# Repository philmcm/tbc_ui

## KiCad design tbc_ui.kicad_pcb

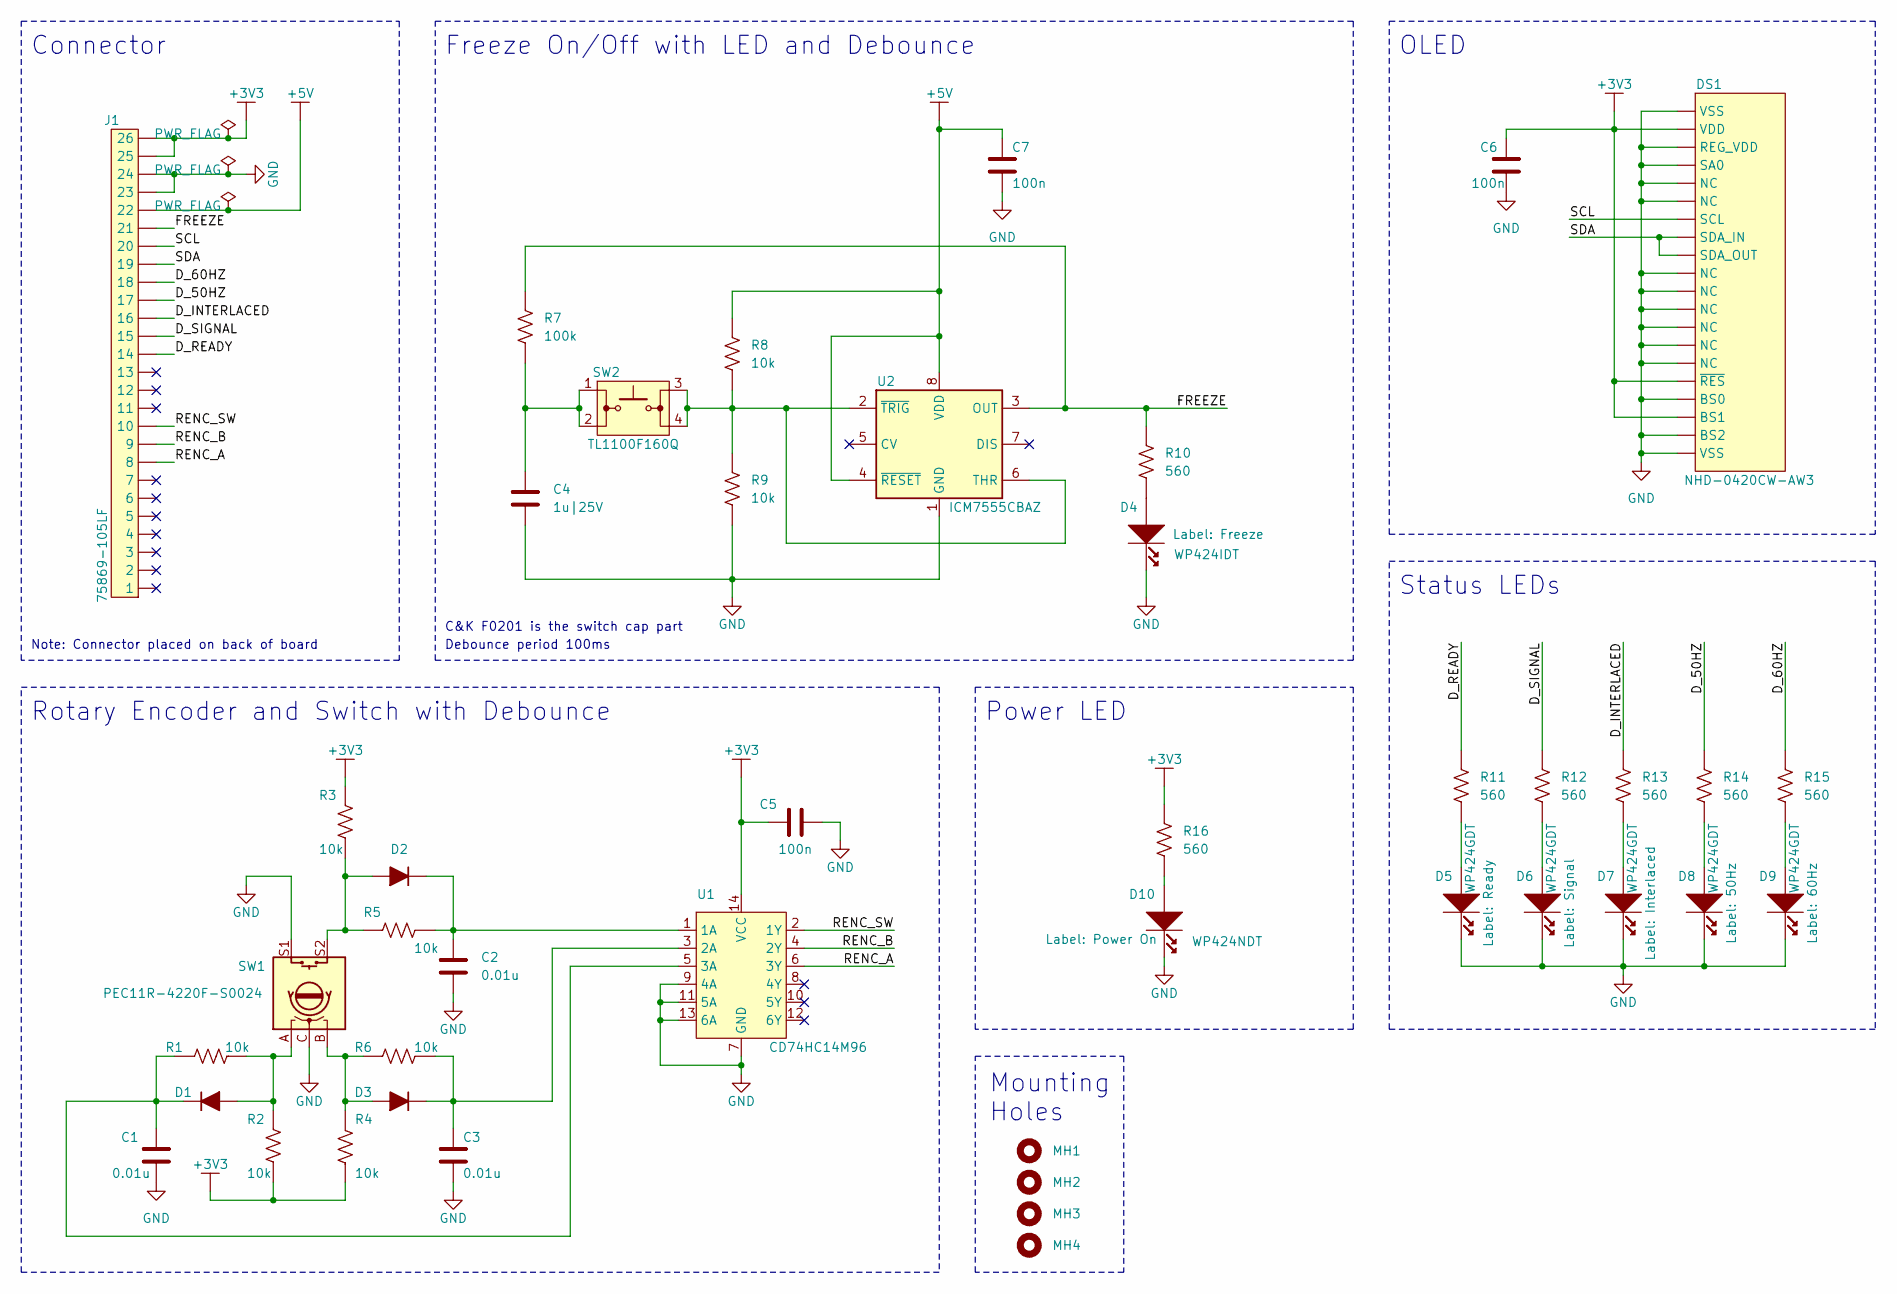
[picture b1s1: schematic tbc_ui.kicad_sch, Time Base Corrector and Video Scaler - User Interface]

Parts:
C1, C2, C3: 0.01u; C0603; Mouser 81-GCM188R71H103KA7J
C4: 1u|25V; C0603; Mouser 81-GCJ188R71E105KA1D
C5, C6, C7: 100n; C0603; Mouser 81-GCJ188R71H104KA2D
D1, D2, D3: 1N4148WS; Mouser 512-1N4148WS
D4: WP424IDT; WP424; Mouser 604-WP424IDT
D5, D6, D7, D8, D9: WP424GDT; WP424; Mouser 604-WP424GDT
D10: WP424NDT; WP424; Mouser 604-WP424NDT
DS1: NHD-0420CW-AW3; NHD-0420CW; Mouser 763-NHD-0420CW-AW3
J1: 75869-105LF; Mouser 649-75869-105LF
MH1, MH2, MH3, MH4: MH_7.4MMNCx3.2MMD; MH_7.4MMCx3.2MMD_NON_COPPER_NPTH
R1, R2, R3, R4, R5, R6, R8, R9: 10k; R0603; Mouser 603-RC0603FR-0710KL
R7: 100k; R0603; Mouser 603-RC0603FR-07100KL
R10, R11, R12, R13, R14, R15, R16: 560; R0603; Mouser 603-RC0603FR-07560RL
SW1: PEC11R-4220F-S0024; PEC11R-4xxxF-Sxxx; Mouser 652-PEC11R-4220F-S24
SW2: TL1100F160Q; TL1100F; Mouser 612-TL1100
U1: CD74HC14M96; SOIC-14; Mouser 595-CD74HC14M96
U2: ICM7555CBAZ; SOIC-8; Mouser 968-ICM7555CBAZ

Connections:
+3V3: C5.1, C6.2, DS1.2 (VDD), DS1.16 (~RES), DS1.18 (BS1), J1.25, J1.26, R2.1, R3.2, R4.2, R16.2, U1.14 (VCC)
+5V: C7.2, J1.22, R8.2, U2.4 (~RESET), U2.8 (VDD)
/D_50HZ: J1.17, R14.2
/D_60HZ: J1.18, R15.2
/D_INTERLACED: J1.16, R13.2
/D_READY: J1.14, R11.2
/D_SIGNAL: J1.15, R12.2
/FREEZE: J1.21, R7.2, R10.2, U2.3 (OUT)
/RENC_A: J1.8, U1.6 (3Y)
/RENC_B: J1.9, U1.4 (2Y)
/RENC_SW: J1.10, U1.2 (1Y)
/SCL: DS1.7 (SCL), J1.20
/SDA: DS1.8 (SDA_IN), DS1.9 (SDA_OUT), J1.19
GND: C1.1, C2.1, C3.1, C4.1, C5.2, C6.1, C7.1, D4.1 (Cathode), D5.1 (Cathode), D6.1 (Cathode), D7.1 (Cathode), D8.1 (Cathode), D9.1 (Cathode), D10.1 (Cathode), DS1.1 (VSS), DS1.3 (REG_VDD), DS1.4 (SA0), DS1.5 (NC), DS1.6 (NC), DS1.10 (NC), DS1.11 (NC), DS1.12 (NC), DS1.13 (NC), DS1.14 (NC), DS1.15 (NC), DS1.17 (BS0), DS1.19 (BS2), DS1.20 (VSS), J1.23, J1.24, R9.1, SW1.C, SW1.S1, U1.7 (GND), U1.9 (4A), U1.11 (5A), U1.13 (6A), U2.1 (GND)
unnamed: C4.2, R7.1, SW2.1, SW2.2
unnamed: D1.2 (A), R1.2, R2.2, SW1.A
unnamed: C1.2, D1.1 (K), R1.1, U1.5 (3A)
unnamed: D2.2 (A), R3.1, R5.2, SW1.S2
unnamed: C2.2, D2.1 (K), R5.1, U1.1 (1A)
unnamed: D3.2 (A), R4.1, R6.2, SW1.B
unnamed: C3.2, D3.1 (K), R6.1, U1.3 (2A)
unnamed: D4.2 (Anode), R10.1
unnamed: D5.2 (Anode), R11.1
unnamed: D6.2 (Anode), R12.1
unnamed: D7.2 (Anode), R13.1
unnamed: D8.2 (Anode), R14.1
unnamed: D9.2 (Anode), R15.1
unnamed: D10.2 (Anode), R16.1
unnamed: R8.1, R9.2, SW2.3, SW2.4, U2.2 (~TRIG), U2.6 (THR)

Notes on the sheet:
Mounting Holes
Connector
OLED
Debounce period 100ms
Freeze On/Off with LED and Debounce
Power LED
Status LEDs
Rotary Encoder and Switch with Debounce
C&K F0201 is the switch cap part
Note: Connector placed on back of board

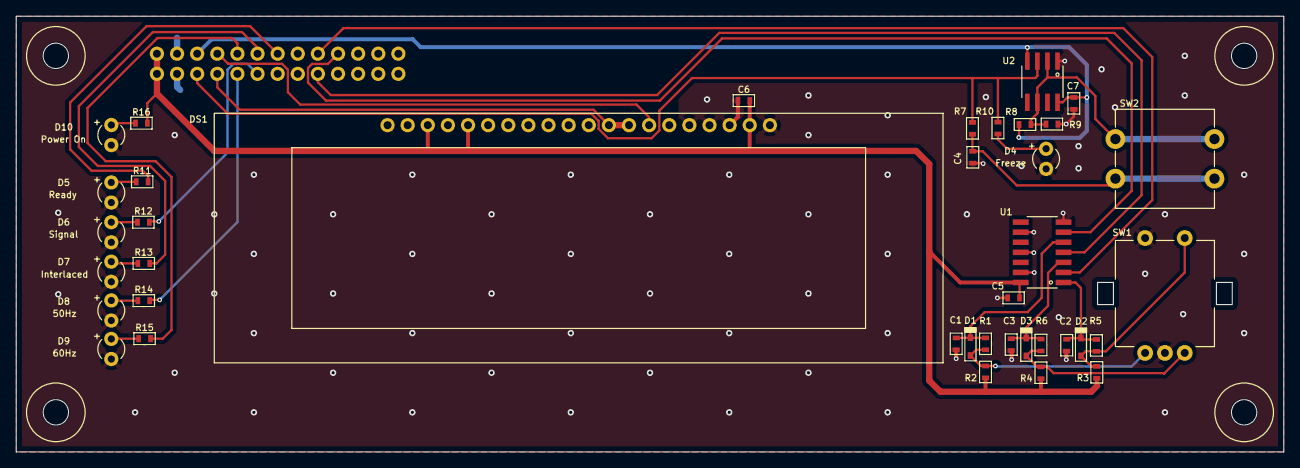
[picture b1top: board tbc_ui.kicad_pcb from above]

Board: 2 copper layers, 160.0 x 55.0 mm, 43 parts (1 on the bottom side), 29 nets.

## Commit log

2024-01-25 annotated and DRC'd schematic
2024-01-25 switched out tactile switch
2024-01-25 updated IDC symbol
2024-01-25 changed 555 to 5V
2024-01-27 pull in symbols after simulation model disabled, re-run ERC
2024-02-22 initial board layout
2024-02-23 additional footprints and layout
2024-02-24 updated to Kicad 8, finished footprints and layouts, erc passed
2024-02-24 added gerbers and drills
2024-07-08 new copper pours
2025-01-18 upgraded Kicad 8.0.8; .gitignore
2025-01-18 Ran DRC, zero errors

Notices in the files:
tbc_ui.kicad_sch:
Enhancements © 2024 Phil McMillan
Original TBC circuit design © 2001 Marcus Gunnarsson
